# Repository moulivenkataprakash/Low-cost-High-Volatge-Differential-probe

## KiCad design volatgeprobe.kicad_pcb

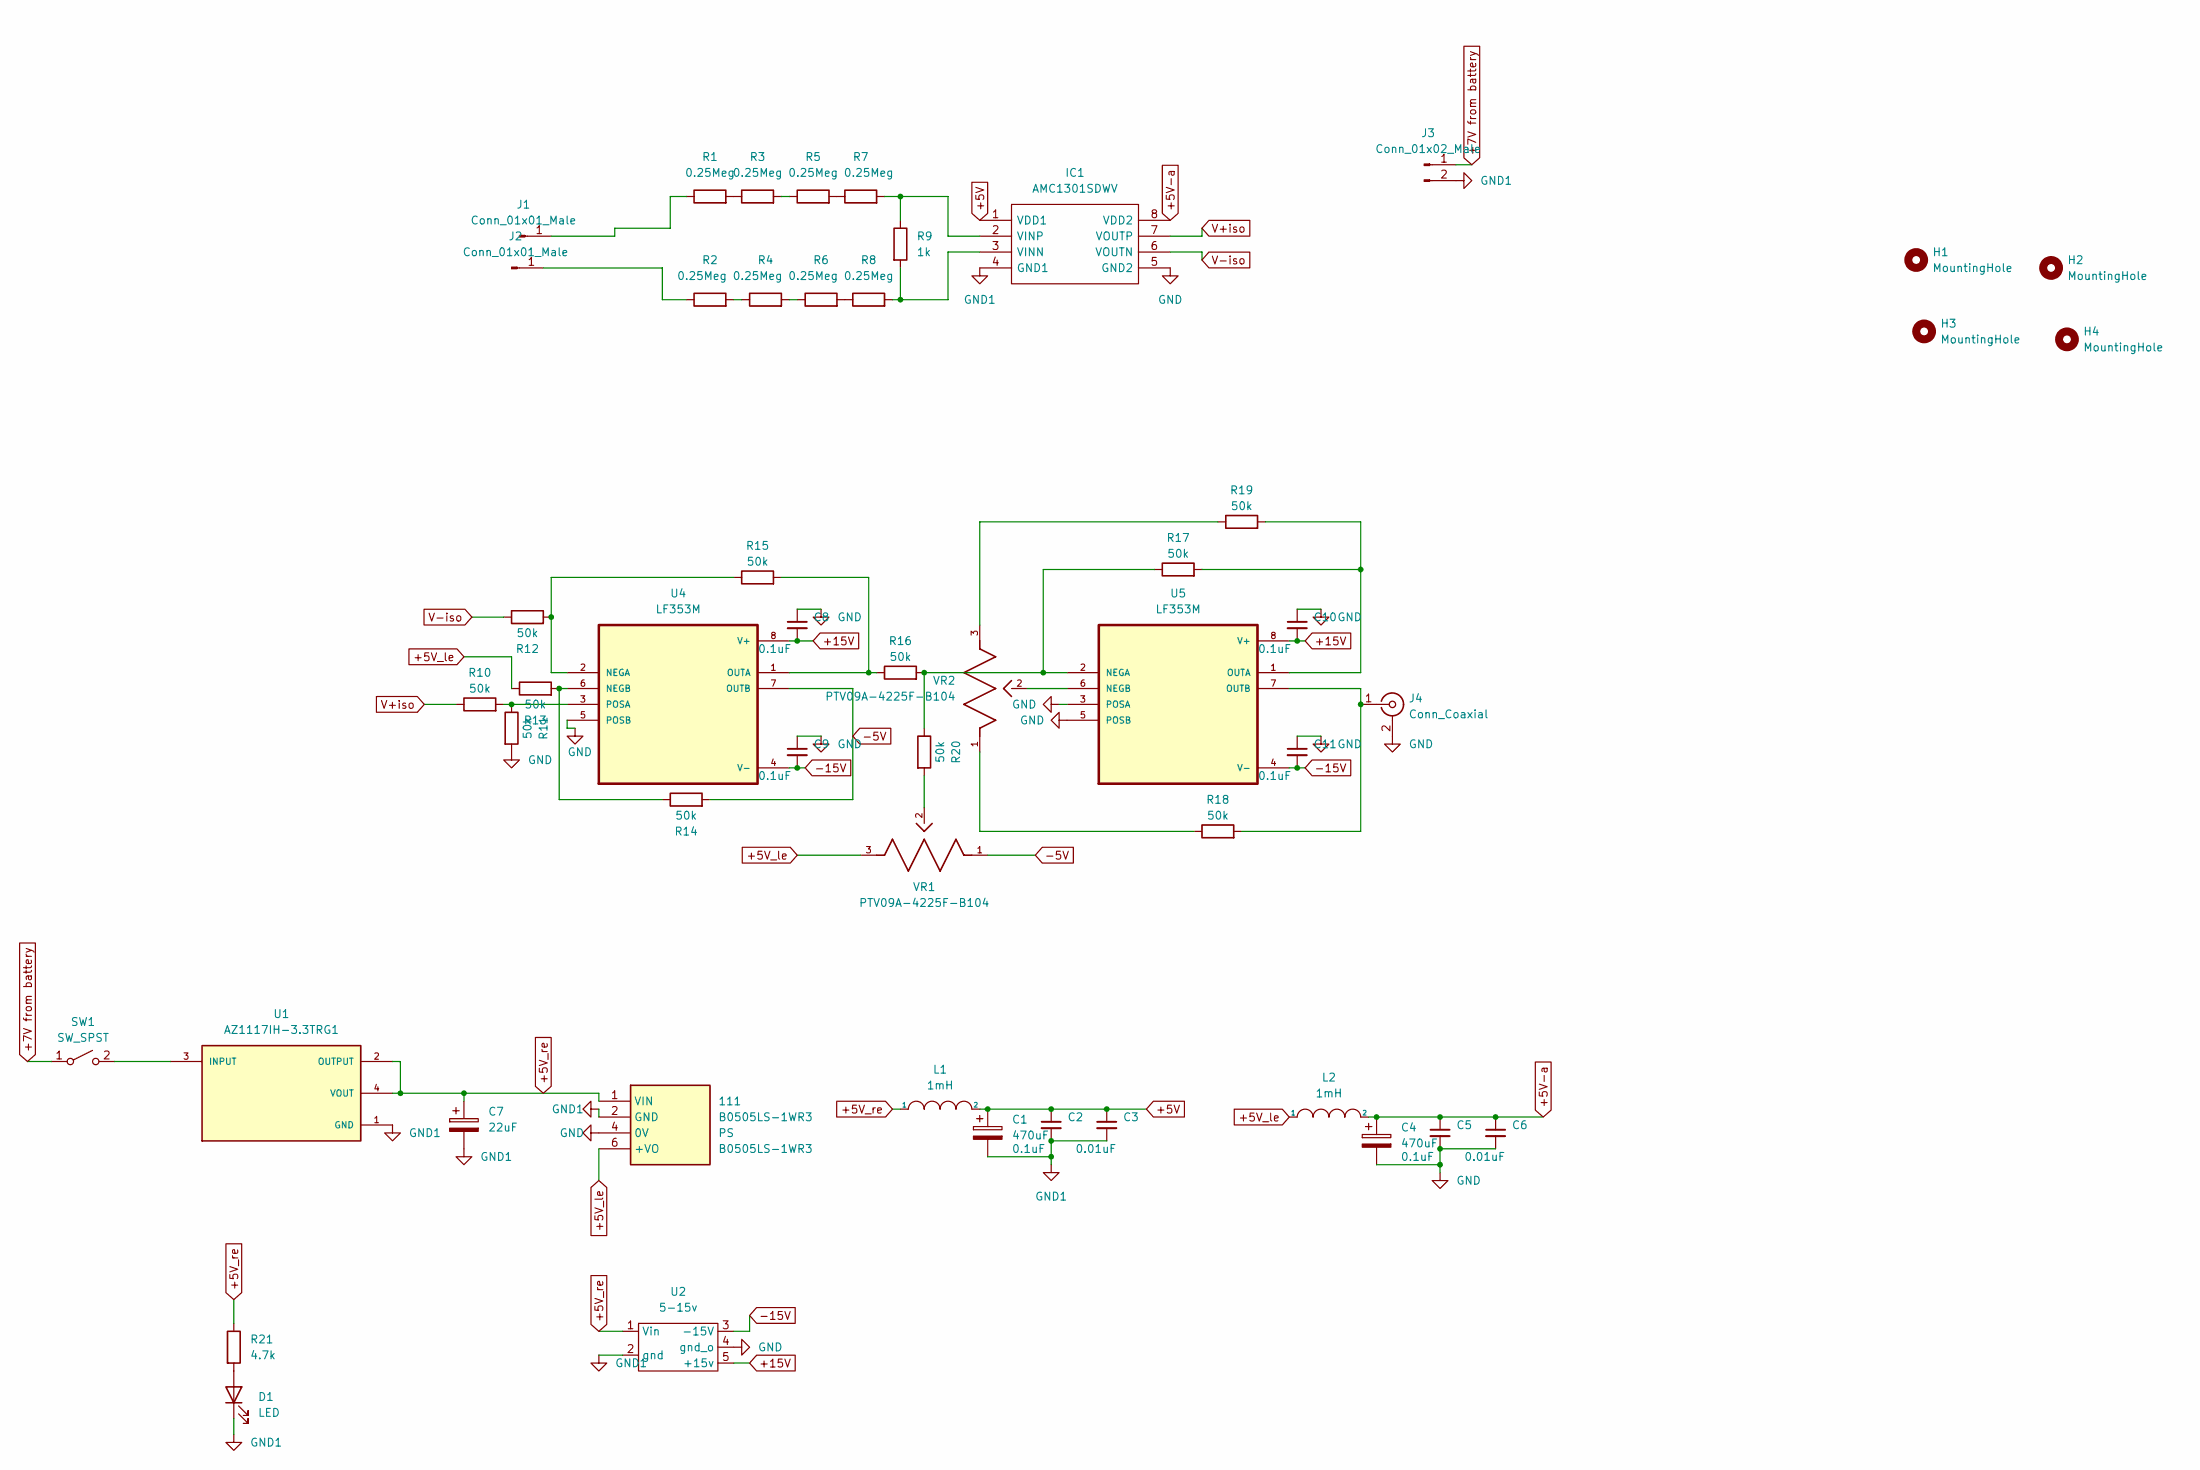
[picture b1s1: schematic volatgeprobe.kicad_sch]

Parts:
111: B0505LS-1WR3; B0505LS1WR3; Manufacturer_Part_Number B0505LS-1WR3
C1, C4: 470uF; CAPAE1030X1050N
C2, C5, C8, C9, C10, C11: 0.1uF; C_0805_2012Metric
C3, C6: 0.01uF; C_0805_2012Metric
C7: 22uF; EEE0GA101SR
D1: LED; LED_D5.0mm
H1, H2, H3, H4: MountingHole; MountingHole_3.2mm_M3
IC1: AMC1301SDWV; SOIC127P1150X280-8N; Manufacturer_Part_Number AMC1301SDWV; Mouser Part Number 595-AMC1301SDWV
J1, J2: Conn_01x01_Male; 1050752001
J3: Conn_01x02_Male; BAT_BK-18650-PC4
J4: Conn_Coaxial; TE_227161-1
L1, L2: 1mH; DR74
R1, R2, R3, R4, R5, R6, R7, R8: 0.25Meg; R_0805_2012Metric
R9: 1k; R_0805_2012Metric
R10, R11, R12, R13, R14, R15, R16, R17, R18, R19, R20: 50k; R_0805_2012Metric
R21: 4.7k; R_0805_2012Metric
SW1: SW_SPST; PinHeader_1x02_P2.54mm_Vertical
U1: AZ1117IH-3.3TRG1; SOT230P700X185-4N; PARTREV 2-2
U2: 5-15v; Converter_DCDC_Murata_NMAxxxxSC_THT
U4, U5: LF353M; SOIC127P599X175-8N
VR1, VR2: PTV09A-4225F-B104; PTV09; PARTNO PTV09A-4225F-B104-ND

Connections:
+5V: C1.1, C2.1, C3.1, IC1.1 (VDD1), L1.2
+5V-a: C4.1, C5.1, C6.1, IC1.8 (VDD2), L2.2
+5V_le: 111.6 (+VO), L2.1, R13.1, VR1.3
+5V_re: 111.1 (VIN), C7.1, L1.1, R21.1, U1.2 (OUTPUT), U1.4 (VOUT), U2.1 (Vin)
+7V from battery: J3.1, SW1.1 (A)
+15V: C8.2, C10.2, U2.5 (+15v), U4.8 (V+), U5.8 (V+)
-5V: R14.2, U4.7 (OUTB), VR1.1
-15V: C9.2, C11.2, U2.3 (-15V), U4.4 (V-), U5.4 (V-)
GND: 111.4 (0V), C4.2, C5.2, C6.2, C8.1, C9.1, C10.1, C11.1, IC1.5 (GND2), J4.2 (Ext), R11.2, U2.4 (gnd_o), U4.5 (POSB), U5.3 (POSA), U5.5 (POSB)
GND1: 111.2 (GND), C1.2, C2.2, C3.2, C7.2, D1.1 (K), IC1.4 (GND1), J3.2, U1.1 (GND), U2.2 (gnd)
unnamed: D1.2 (A), R21.2
unnamed: IC1.3 (VINN), R8.2, R9.2
unnamed: IC1.2 (VINP), R7.2, R9.1
unnamed: J1.1, R1.1
unnamed: J2.1, R2.1
unnamed: J4.1 (In), R18.2, U5.7 (OUTB)
unnamed: R1.2, R3.1
unnamed: R2.2, R4.1
unnamed: R3.2, R5.1
unnamed: R4.2, R6.1
unnamed: R5.2, R7.1
unnamed: R6.2, R8.1
unnamed: R18.1, VR2.1
unnamed: R19.1, VR2.3
unnamed: R20.2, VR1.2
unnamed: SW1.2 (B), U1.3 (INPUT)
unnamed: R12.2, R15.1, U4.2 (NEGA)
unnamed: R13.2, R14.1, U4.6 (NEGB)
unnamed: R15.2, R16.1, U4.1 (OUTA)
unnamed: R10.2, R11.1, U4.3 (POSA)
unnamed: R16.2, R17.1, R20.1, U5.2 (NEGA)
unnamed: U5.6 (NEGB), VR2.2
unnamed: R17.2, R19.2, U5.1 (OUTA)
V+iso: IC1.7 (VOUTP), R10.1
V-iso: IC1.6 (VOUTN), R12.1

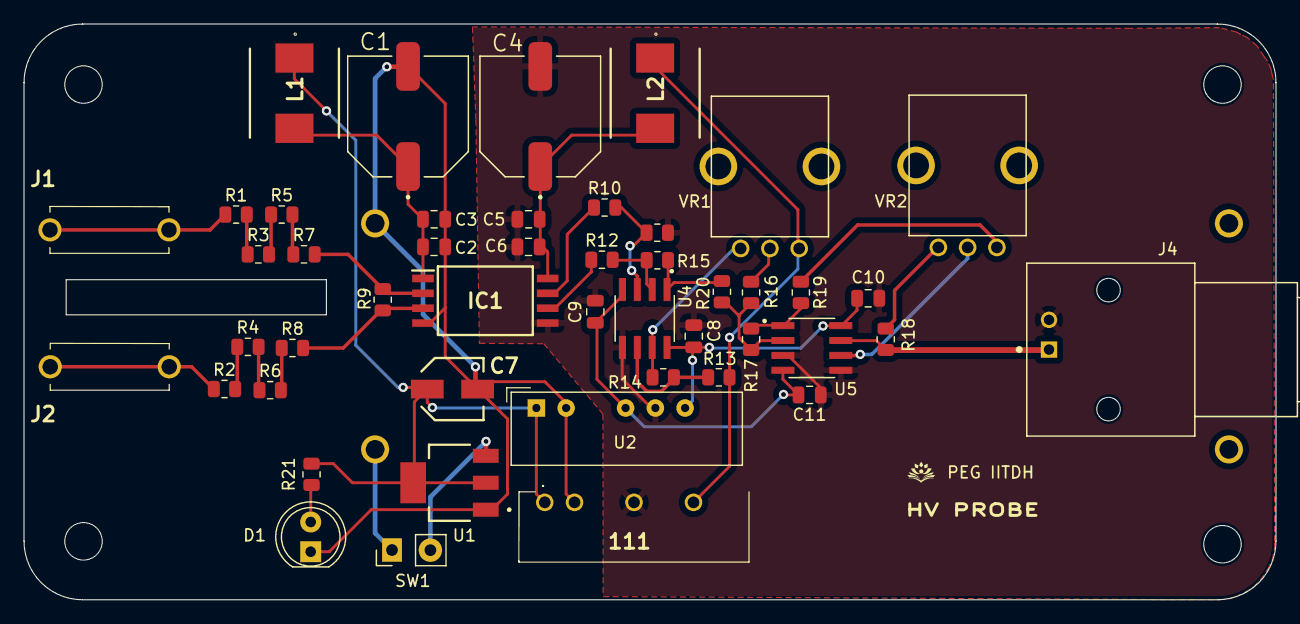
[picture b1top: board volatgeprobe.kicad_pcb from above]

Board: 2 copper layers, 106.9 x 49.2 mm, 52 parts (1 on the bottom side), 35 nets.

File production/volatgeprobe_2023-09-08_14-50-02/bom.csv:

Designator,Footprint,Quantity,Value,LCSC Part #
111,B0505LS1WR3,1,B0505LS-1WR3,
"C1, C4",CAPAE1030X1050N,2,470uF,
"C10, C11, C2, C5, C8, C9",0805,6,0.1uF,
"C3, C6",0805,2,0.01uF,
C7,EEE0GA101SR,1,22uF,
D1,LED_D5.0mm,1,LED,
"H1, H2, H3, H4",MountingHole_3.2mm_M3,4,MountingHole,
IC1,SOIC127P1150X280-8N,1,AMC1301SDWV,
"J1, J2",1050752001,2,Conn_01x01_Male,
J3,BAT_BK-18650-PC4,1,Conn_01x02_Male,
J4,TE_227161-1,1,Conn_Coaxial,
"L1, L2",DR74,2,1mH,
"R1, R2, R3, R4, R5, R6, R7, R8",0805,8,0.25Meg,
"R10, R11, R12, R13, R14, R15, R16, R17, R18, R19, R20",0805,11,50k,
R21,0805,1,4.7k,
R9,0805,1,1k,
SW1,PinHeader_1x02_P2.54mm_Vertical,1,SW_SPST,
U1,SOT230P700X185-4N,1,AZ1117IH-3.3TRG1,
U2,Converter_DCDC_Murata_NMAxxxxSC_THT,1,5-15v,
"U4, U5",SOIC127P599X175-8N,2,LF353M,
"VR1, VR2",PTV09,2,PTV09A-4225F-B104,

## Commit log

2023-09-04 added all files
2023-09-04 shorted ldo outs
2023-09-04 changed
2023-09-07 inductors foot print changed
2023-09-08 logo added
2023-09-14 battery_3D_added
2023-09-25 names
